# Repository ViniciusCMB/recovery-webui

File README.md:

# Recovery WebUI

Sistema de rastreamento e recuperação em tempo real para foguetes experimentais, desenvolvido para monitorar telemetria via comunicação serial LoRa e visualizar dados em interface web.

## 📋 Visão Geral

O Recovery WebUI é uma aplicação Flask que fornece uma interface web para monitoramento em tempo real de foguetes experimentais. O sistema recebe dados de telemetria via comunicação serial (tipicamente através de módulos LoRa), processa as informações e as exibe em um mapa interativo, permitindo o rastreamento da posição, altitude, e outros parâmetros importantes durante o voo.

### Funcionalidades Principais

- 🗺️ **Visualização em Mapa Interativo**: Mapa com múltiplas camadas (Google Satélite, Google Streets, OpenStreetMap)
- 📡 **Rastreamento em Tempo Real**: Comunicação via WebSocket para atualizações instantâneas
- 📊 **Registro de Dados**: Armazenamento automático de telemetria em formato CSV
- 🚀 **Suporte Dual**: Rastreamento simultâneo de foguete (#100) e satélite (#261)
- 📈 **Histórico de Voo**: Tabelas com histórico completo de dados recebidos
- 🔌 **Comunicação Serial**: Integração com dispositivos via porta serial (LoRa)

### Dados Monitorados

#### Foguete (TEAM_ID #100)

- Posição GPS (latitude, longitude)
- Altitude barométrica
- Número de satélites GPS
- Status do paraquedas
- RSSI (intensidade do sinal)

#### Satélite (TEAM_ID #261)

- Posição GPS (latitude, longitude)
- Altitude
- Temperatura
- Umidade relativa
- Pressão atmosférica
- Número de satélites GPS
- RSSI (intensidade do sinal)

## 🚀 Início Rápido

### Pré-requisitos

- Python 3.7 ou superior
- Porta serial disponível (para comunicação com o módulo LoRa)
- Navegador web moderno

### Instalação

1. Clone o repositório:

```bash
git clone <url-do-repositorio>
cd recovery-webui
```

2. Instale as dependências:

```bash
pip install -r requirements.txt
```

### Uso

1. Conecte o módulo LoRa receptor ao computador via USB

2. Execute a aplicação:

```bash
cd app
python app.py
```

3. Selecione a porta serial quando solicitado:

```
Portas seriais disponíveis:
1: /dev/ttyACM0
2: /dev/ttyUSB0
Selecione a porta serial (número): 1
```

4. O navegador abrirá automaticamente em `http://localhost:5000`

5. Acesse as diferentes visualizações:
   - `/` - Dados do foguete principal
   - `/satellite` - Dados do satélite

## 📁 Estrutura do Projeto

```
recovery-webui/
├── app/
│   ├── app.py              # Aplicação Flask principal
│   ├── module/
│   │   ├── __init__.py
│   │   └── SerialCOM.py    # Módulo de comunicação serial
│   ├── static/
│   │   ├── css/            # Estilos
│   │   └── js/
│   │       └── app.js      # Lógica do cliente (WebSocket, mapa)
│   ├── templates/
│   │   ├── base.html       # Template base
│   │   ├── index.html      # Página do foguete
│   │   └── satellite.html  # Página do satélite
│   └── logs/
│       └── log.csv         # Logs de telemetria
├── requirements.txt        # Dependências Python
└── README.md              # Este arquivo
```

## 🛠️ Tecnologias Utilizadas

### Backend

- **Flask** - Framework web Python
- **Flask-SocketIO** - Comunicação WebSocket em tempo real
- **PySerial** - Comunicação serial com hardware

### Frontend

- **Leaflet.js** - Biblioteca de mapas interativos
- **Socket.IO** - Cliente WebSocket
- **jQuery** - Manipulação do DOM
- **Font Awesome** - Ícones

## 📡 Protocolo de Comunicação

O sistema espera dados no seguinte formato CSV via serial:

```
TEAM_ID,millis,count,altp,temp,umi,p,gp,gr,gy,ap,ar,ay,hora,data,alt,lat,lon,sat,rssi
```

Onde:

- `TEAM_ID`: Identificador do dispositivo (#100 para foguete, #261 para satélite)
- `millis`: Tempo em milissegundos desde o boot
- `count`: Contador de pacotes
- `altp`: Altitude barométrica
- `temp`: Temperatura (°C)
- `umi`: Umidade relativa (%)
- `p`: Pressão atmosférica (hPa)
- `gp`, `gr`, `gy`: Dados do giroscópio (pitch, roll, yaw)
- `ap`, `ar`, `ay`: Dados do acelerômetro (x, y, z)
- `hora`, `data`: Hora e data do GPS
- `alt`: Altitude GPS (m)
- `lat`, `lon`: Coordenadas GPS
- `sat`: Número de satélites GPS

- `rssi`: Intensidade do sinal LoRa

## 📚 Documentação Adicional

Para informações mais detalhadas, consulte a pasta `docs/`:

- [Guia de Instalação](docs/installation.md) - Instalação detalhada e configuração
- [Arquitetura do Sistema](docs/architecture.md) - Detalhes técnicos da arquitetura
- [Documentação da API](docs/api.md) - Endpoints e eventos WebSocket
- [Guia de Desenvolvimento](docs/development.md) - Contribuindo para o projeto

## 🐛 Solução de Problemas

### Porta serial não encontrada

- Verifique se o dispositivo está conectado
- Em Linux, você pode precisar de permissões: `sudo usermod -a -G dialout $USER`
- Verifique se o driver CH340/CP2102 está instalado (dependendo do módulo)

### Dados não aparecem no mapa

- Verifique se o formato dos dados serial está correto
- Confira o console do navegador (F12) para erros JavaScript
- Verifique os logs do servidor no terminal

### Navegador não abre automaticamente

- Abra manualmente: `http://localhost:5000`
- Verifique se a porta 5000 não está em uso

## 🤝 Contribuindo

Contribuições são bem-vindas! Por favor:

1. Faça um fork do projeto
2. Crie uma branch para sua feature (`git checkout -b feature/MinhaFeature`)
3. Commit suas mudanças (`git commit -m 'Adiciona MinhaFeature'`)
4. Push para a branch (`git push origin feature/MinhaFeature`)
5. Abra um Pull Request

Leia nosso [Guia de Contribuição](CONTRIBUTING.md) para mais detalhes sobre padrões de código, processo de desenvolvimento e como reportar bugs.

## 📝 Licença

Este projeto é open source e está disponível para uso educacional e experimental.

## 🔗 Projetos Relacionados

- [flight-computer](../flight-computer) - Firmware do computador de bordo do foguete

## 📧 Contato

Para dúvidas ou sugestões, abra uma issue no repositório.

---

Desenvolvido para competições e experimentos de foguetemodelismo 🚀

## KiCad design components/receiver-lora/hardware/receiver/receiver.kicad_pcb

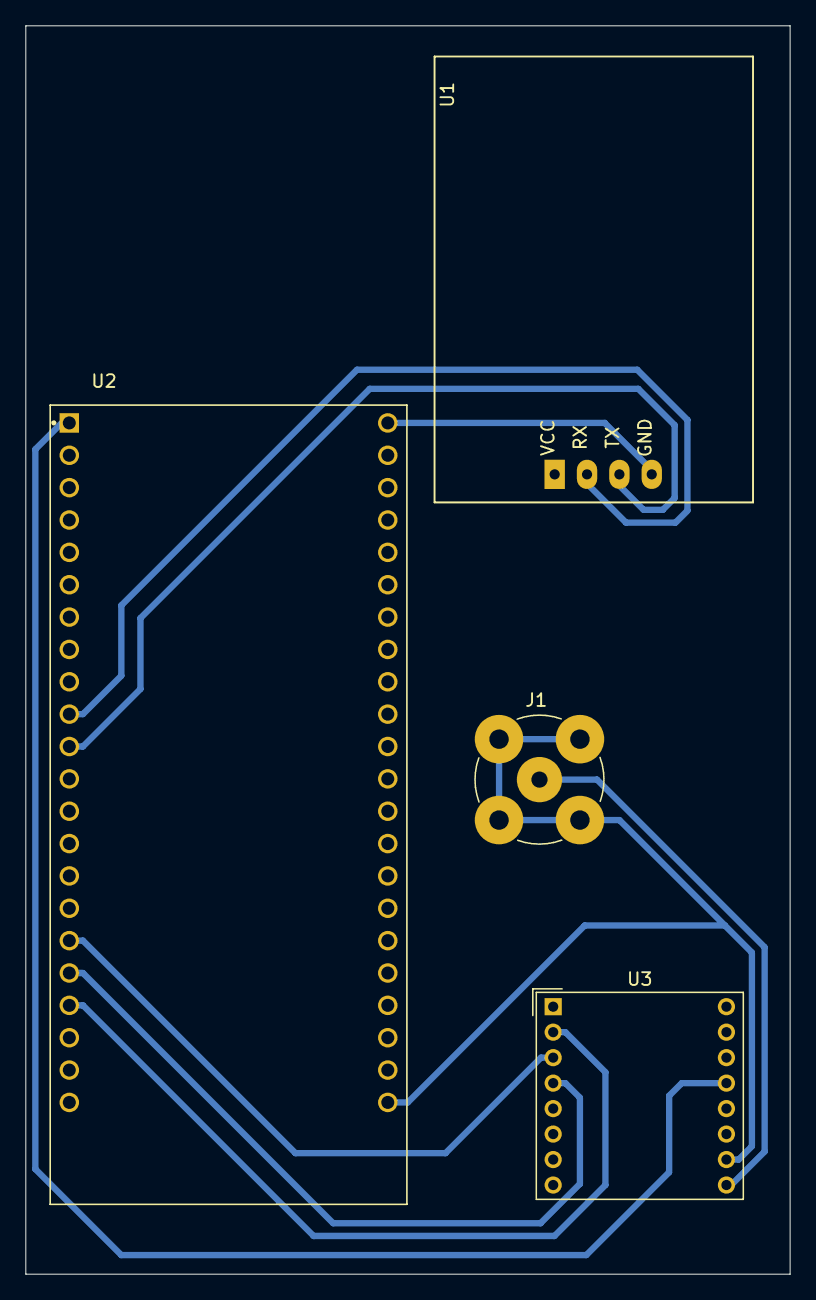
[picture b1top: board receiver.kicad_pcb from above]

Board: 2 copper layers, 60.0 x 98.0 mm, 4 parts (0 on the bottom side), 11 nets.

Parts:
J1: Conn_Coaxial_Small; BNC_TEConnectivity_1478204_Vertical
U1: GY-NEO6MV2
U2: ESP32-S3-DEVKITC-1-N8R8
U3: RFM95W-915S2; HOPERF_RFM9XW_THT

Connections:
/RFID_CS: U2.J1_16 (GPIO10), U3.5 (NSS)
/RFID_RST: U2.J1_15 (GPIO9), U3.6 (RESET)
/SPI_MISO: U2.J1_19 (GPIO13), U3.2 (MISO)
/SPI_MOSI: U2.J1_17 (GPIO11), U3.3 (MOSI)
/SPI_SCK: U2.J1_18 (GPIO12), U3.4 (SCK)
unnamed: J1.2 (Ext), U1.4 (GND), U2.J3_1 (GND), U3.10 (GND)
unnamed: J1.1 (In), U3.9 (ANT)
unnamed: U1.2 (RX), U2.J1_10 (GPIO17)
unnamed: U1.3 (TX), U2.J1_11 (GPIO18)
unnamed: U1.1 (VCC), U2.J1_21 (5V0)
unnamed: U2.J1_1 (3V3), U3.13 (3.3V)
